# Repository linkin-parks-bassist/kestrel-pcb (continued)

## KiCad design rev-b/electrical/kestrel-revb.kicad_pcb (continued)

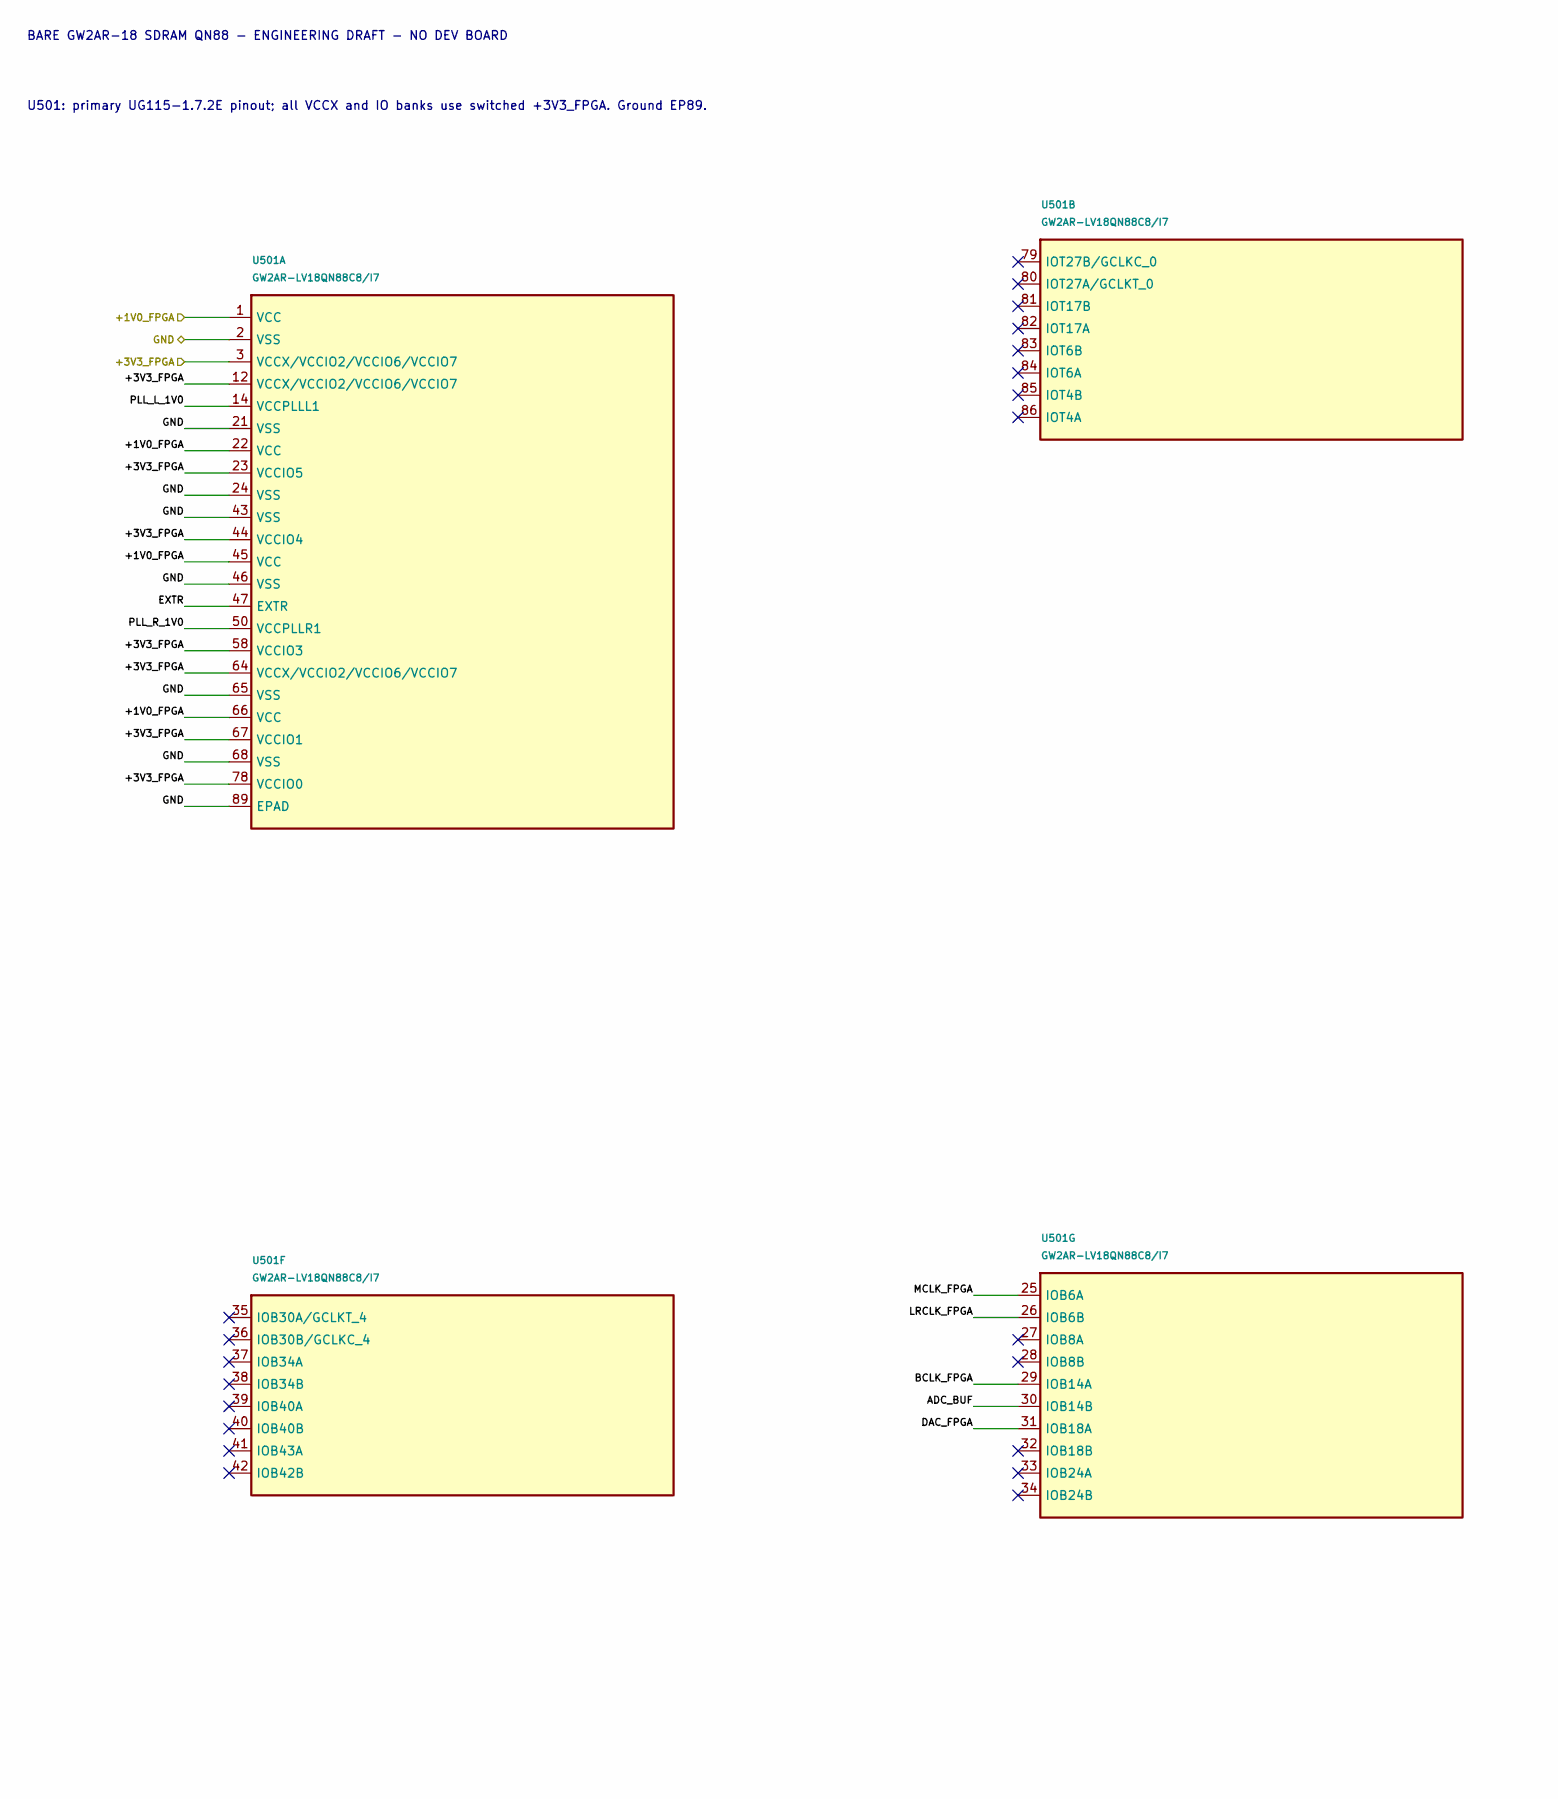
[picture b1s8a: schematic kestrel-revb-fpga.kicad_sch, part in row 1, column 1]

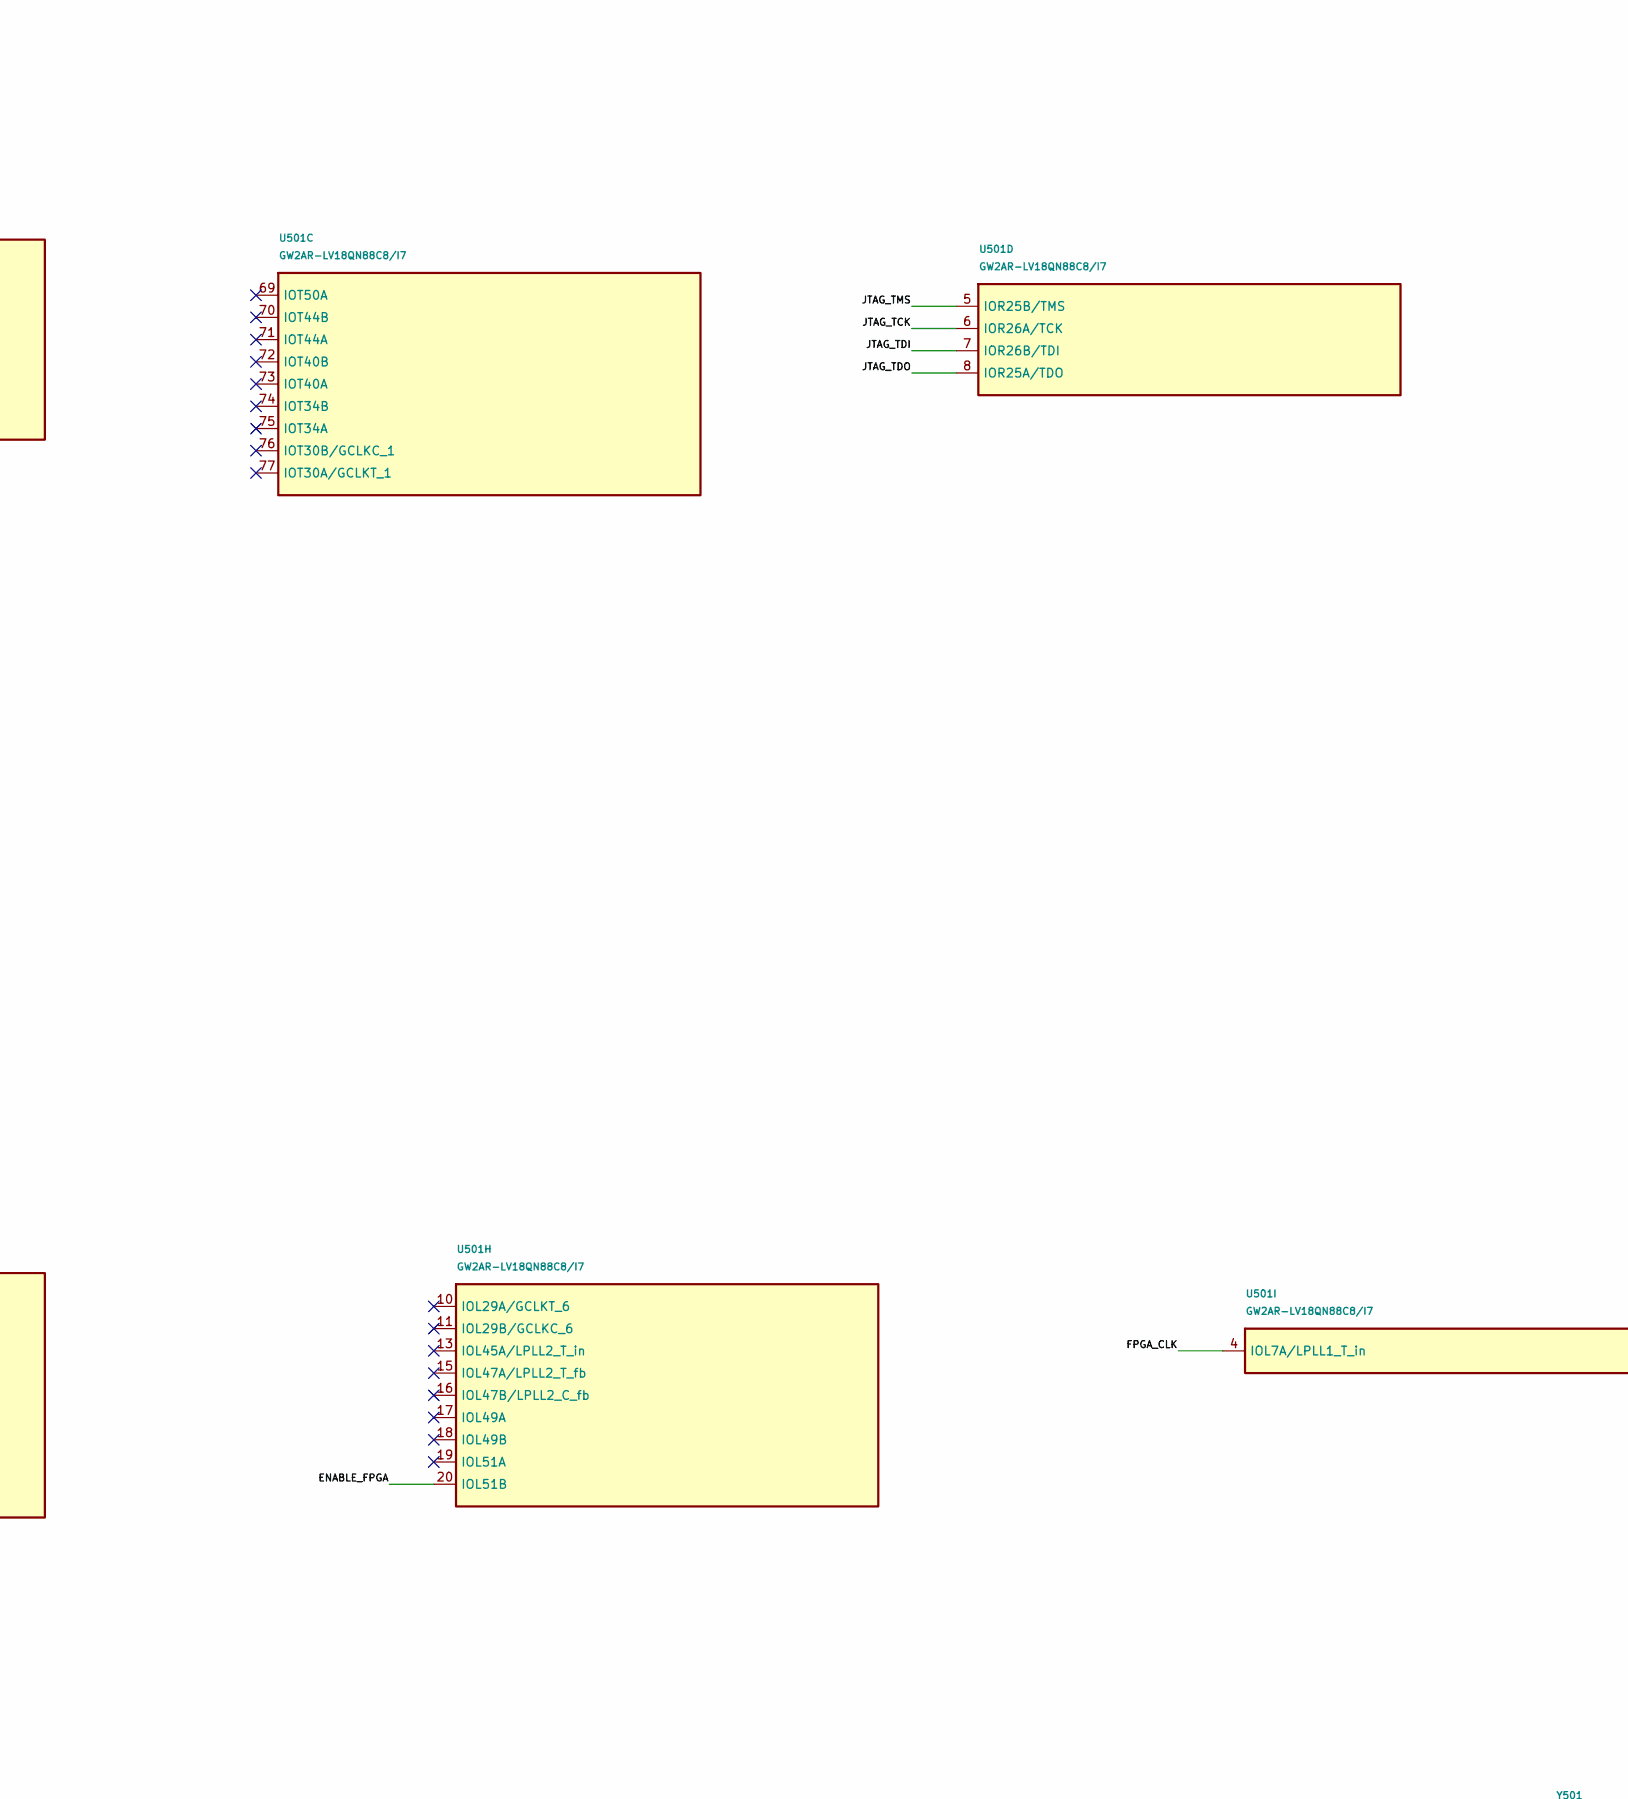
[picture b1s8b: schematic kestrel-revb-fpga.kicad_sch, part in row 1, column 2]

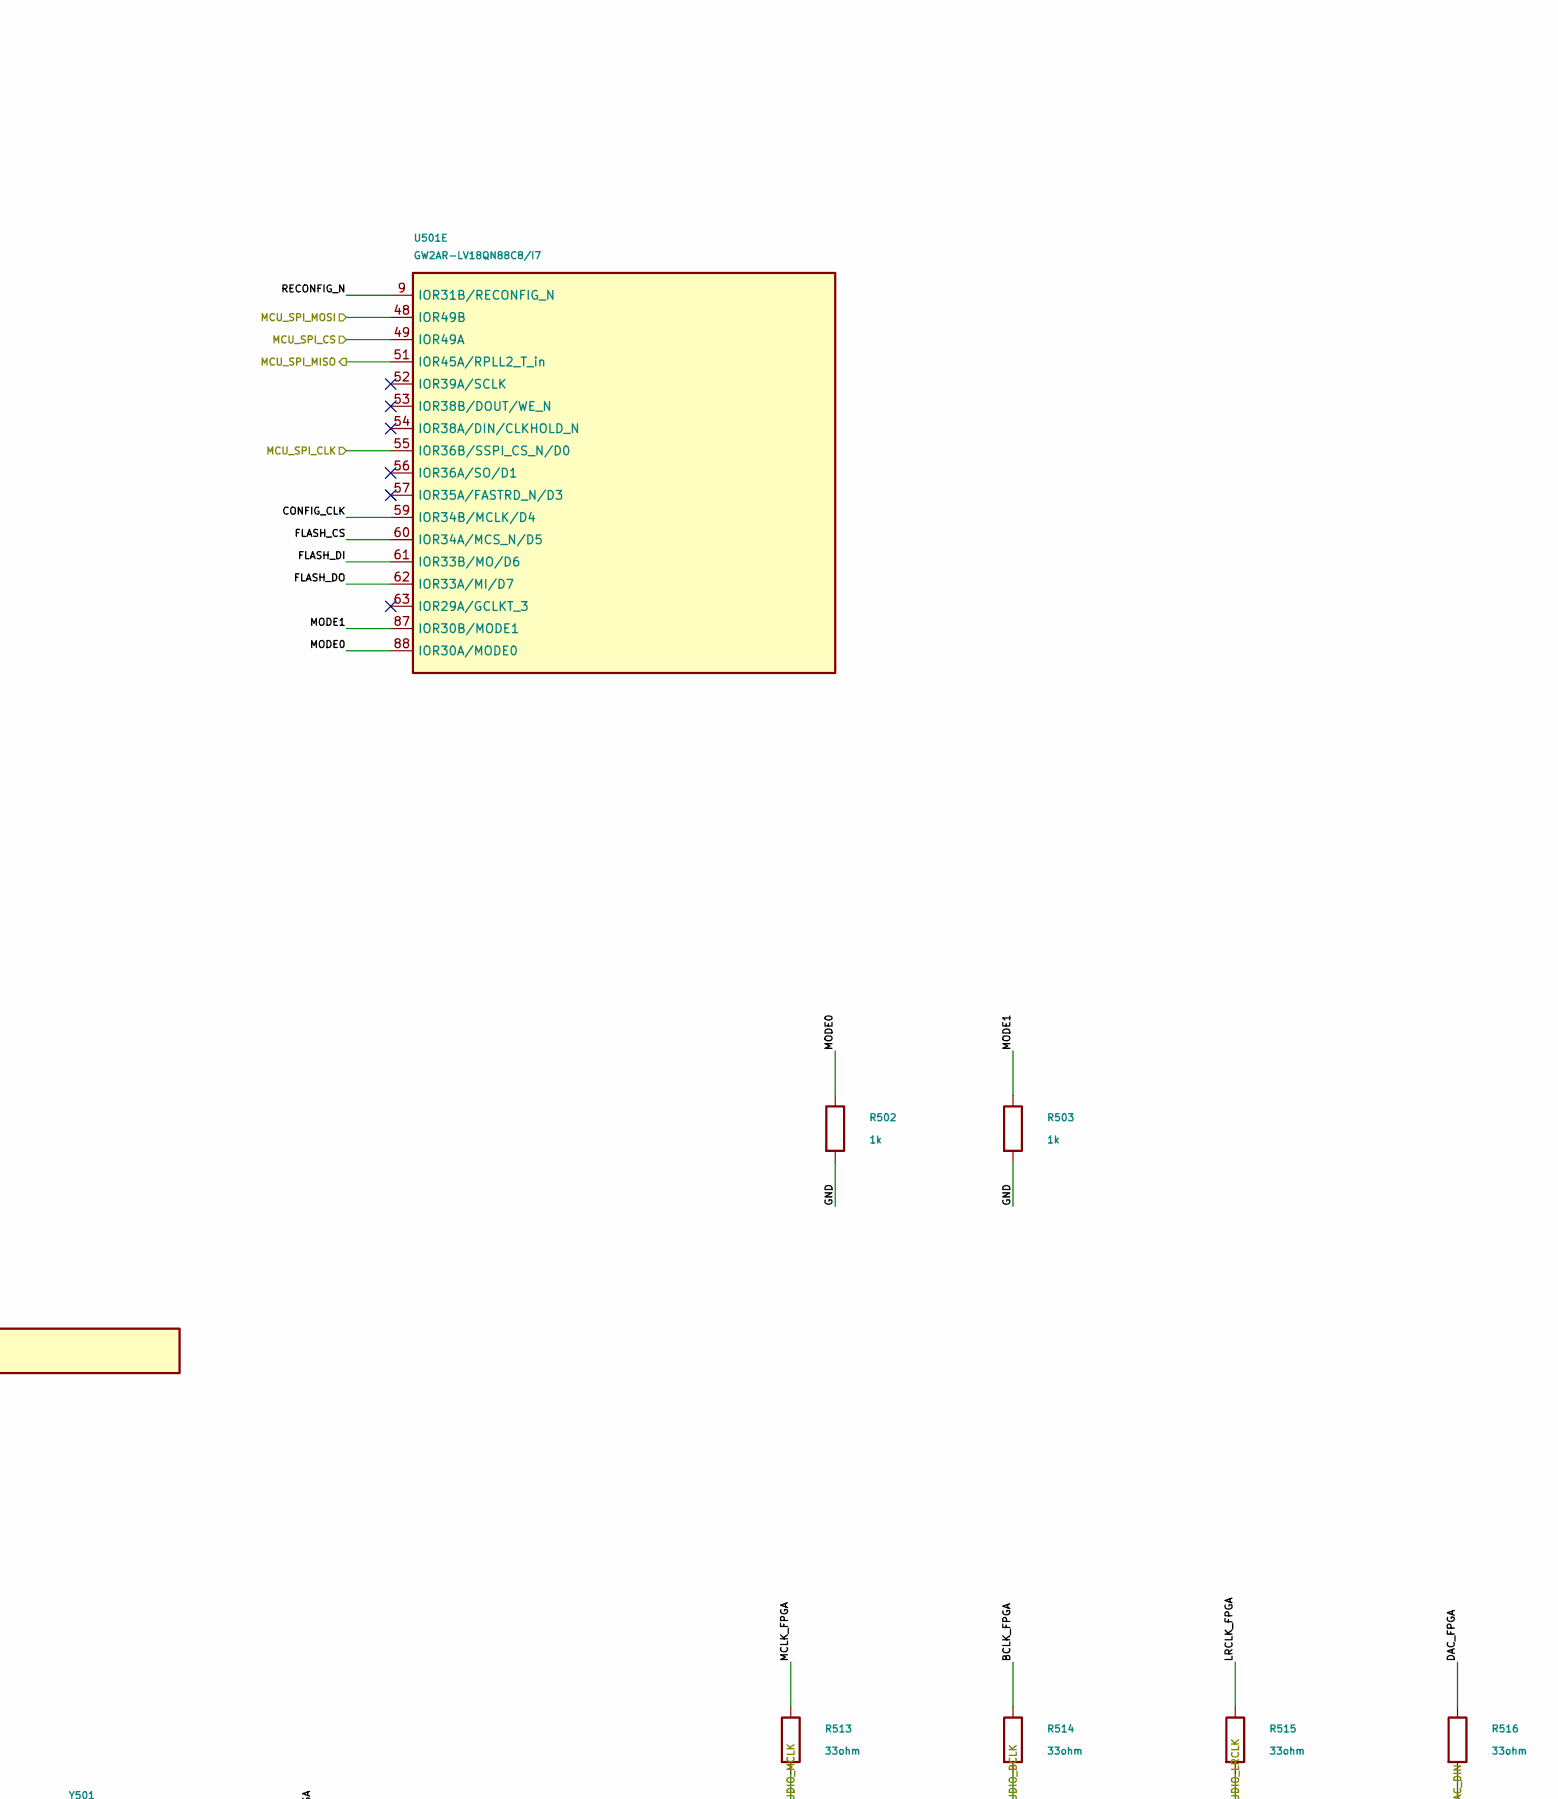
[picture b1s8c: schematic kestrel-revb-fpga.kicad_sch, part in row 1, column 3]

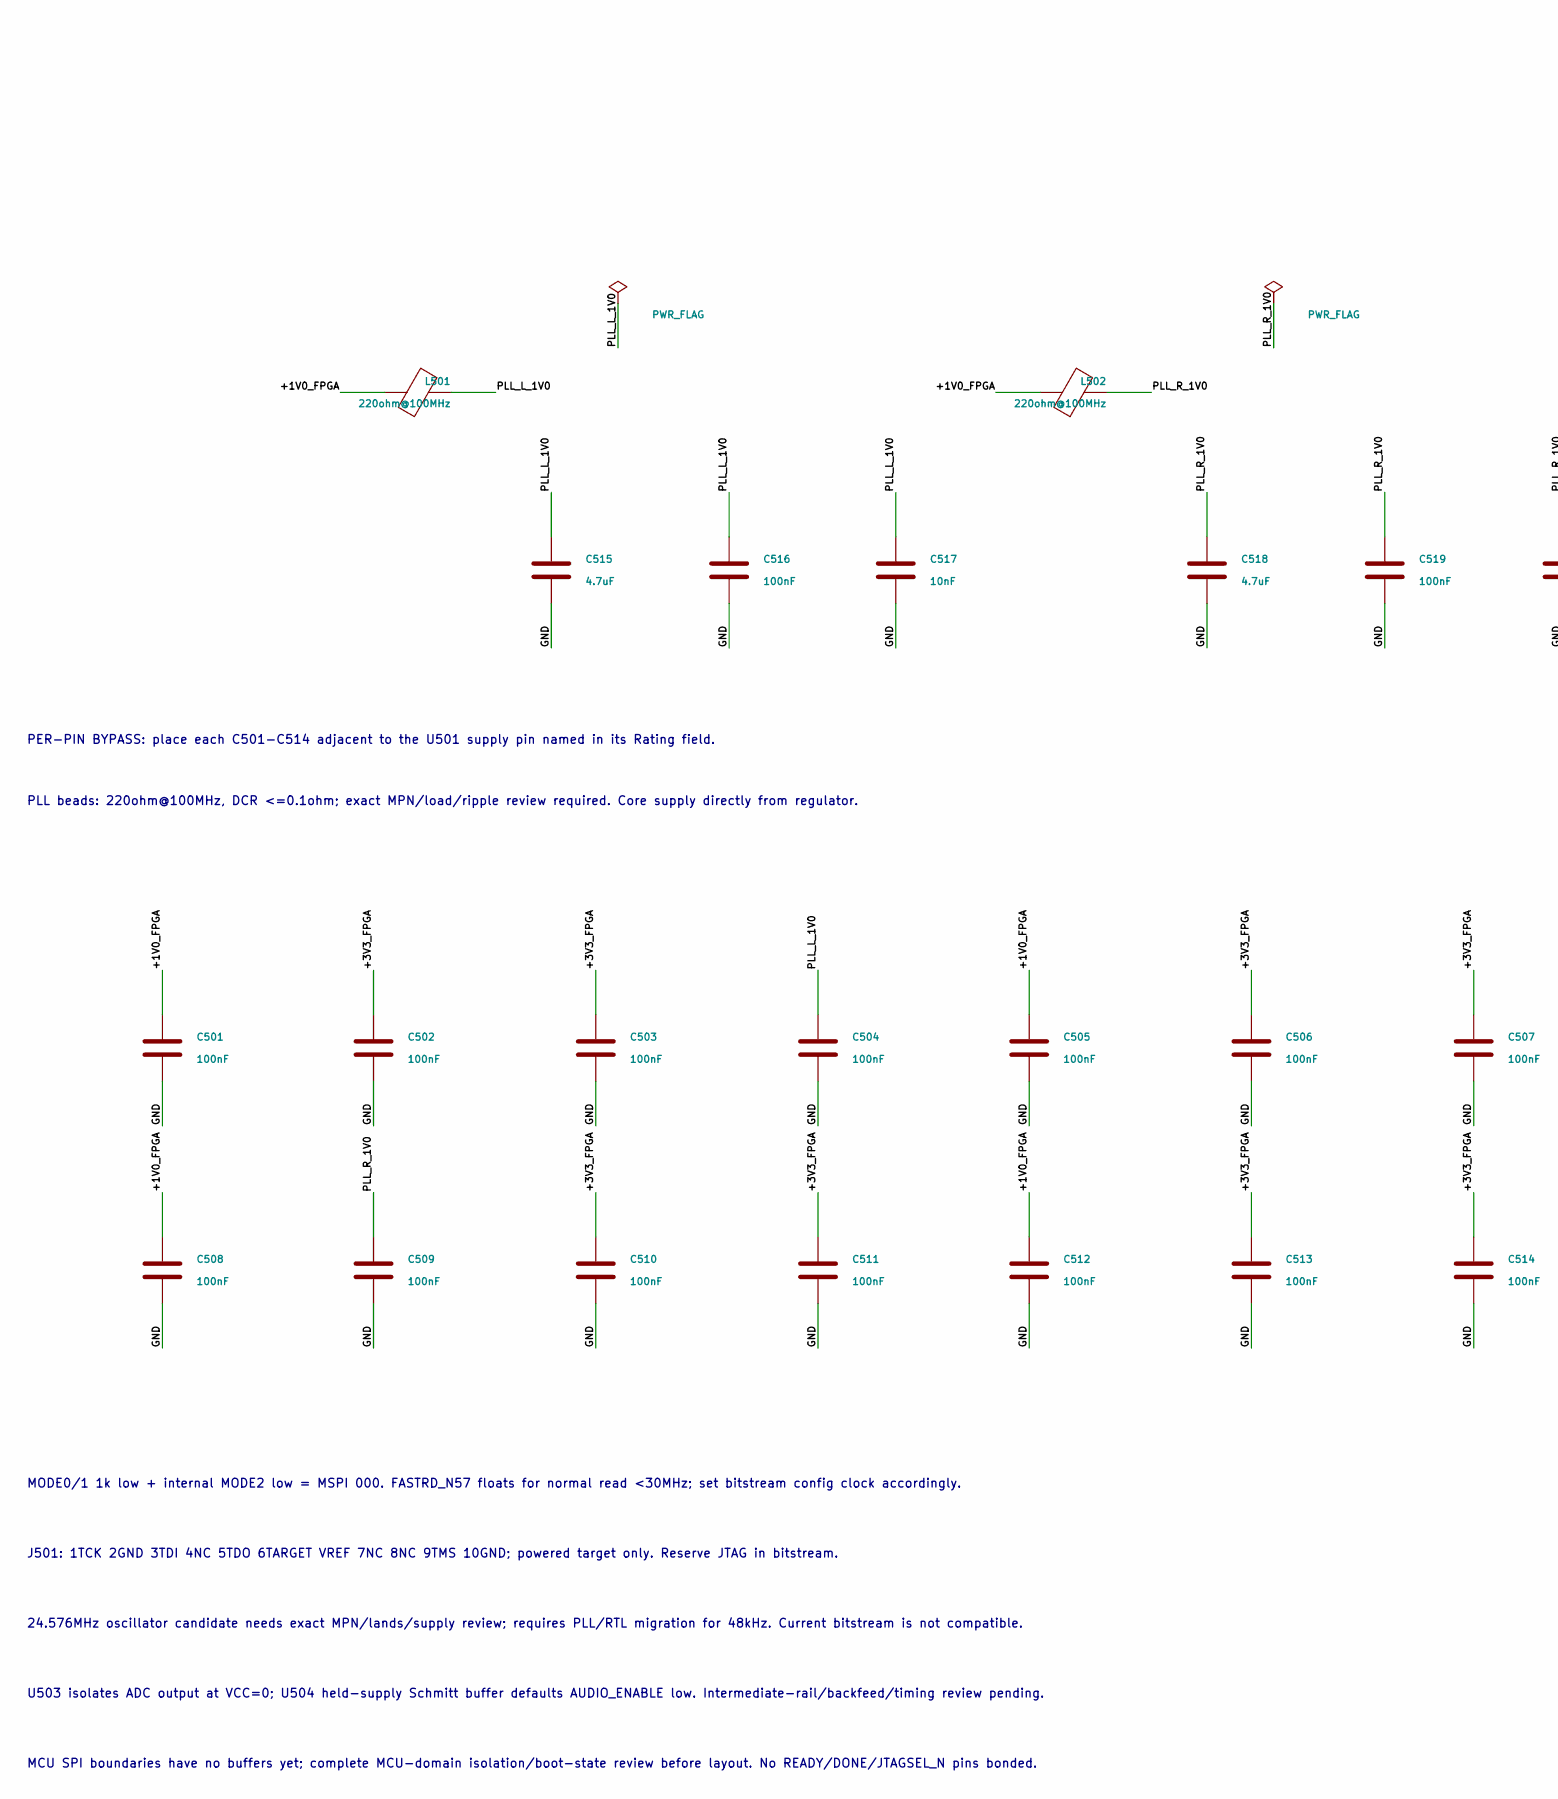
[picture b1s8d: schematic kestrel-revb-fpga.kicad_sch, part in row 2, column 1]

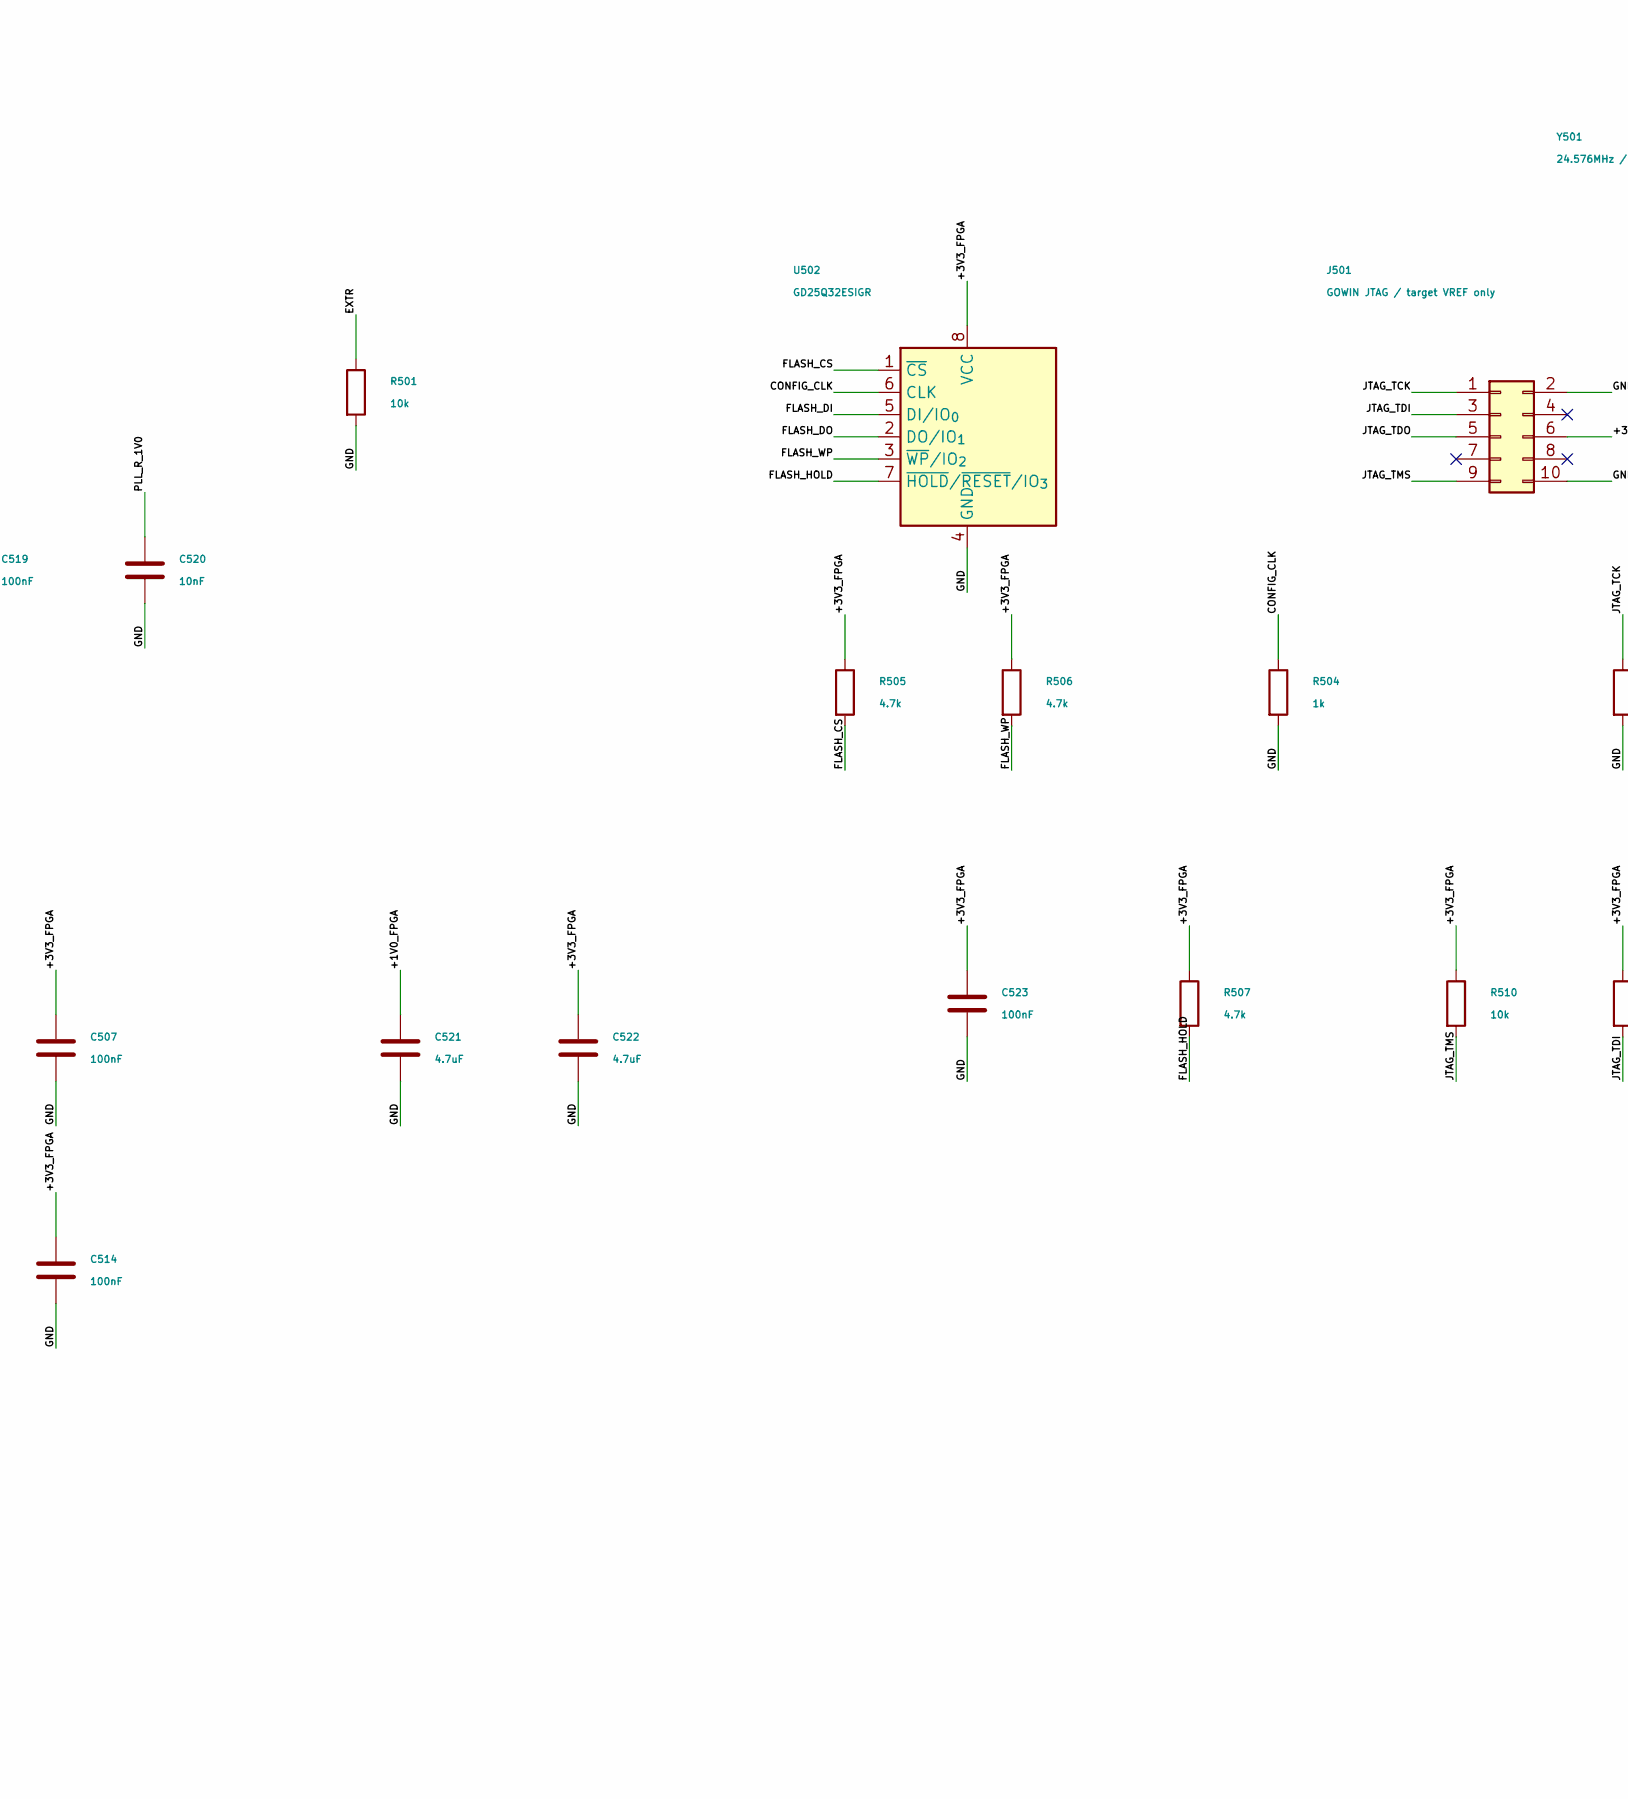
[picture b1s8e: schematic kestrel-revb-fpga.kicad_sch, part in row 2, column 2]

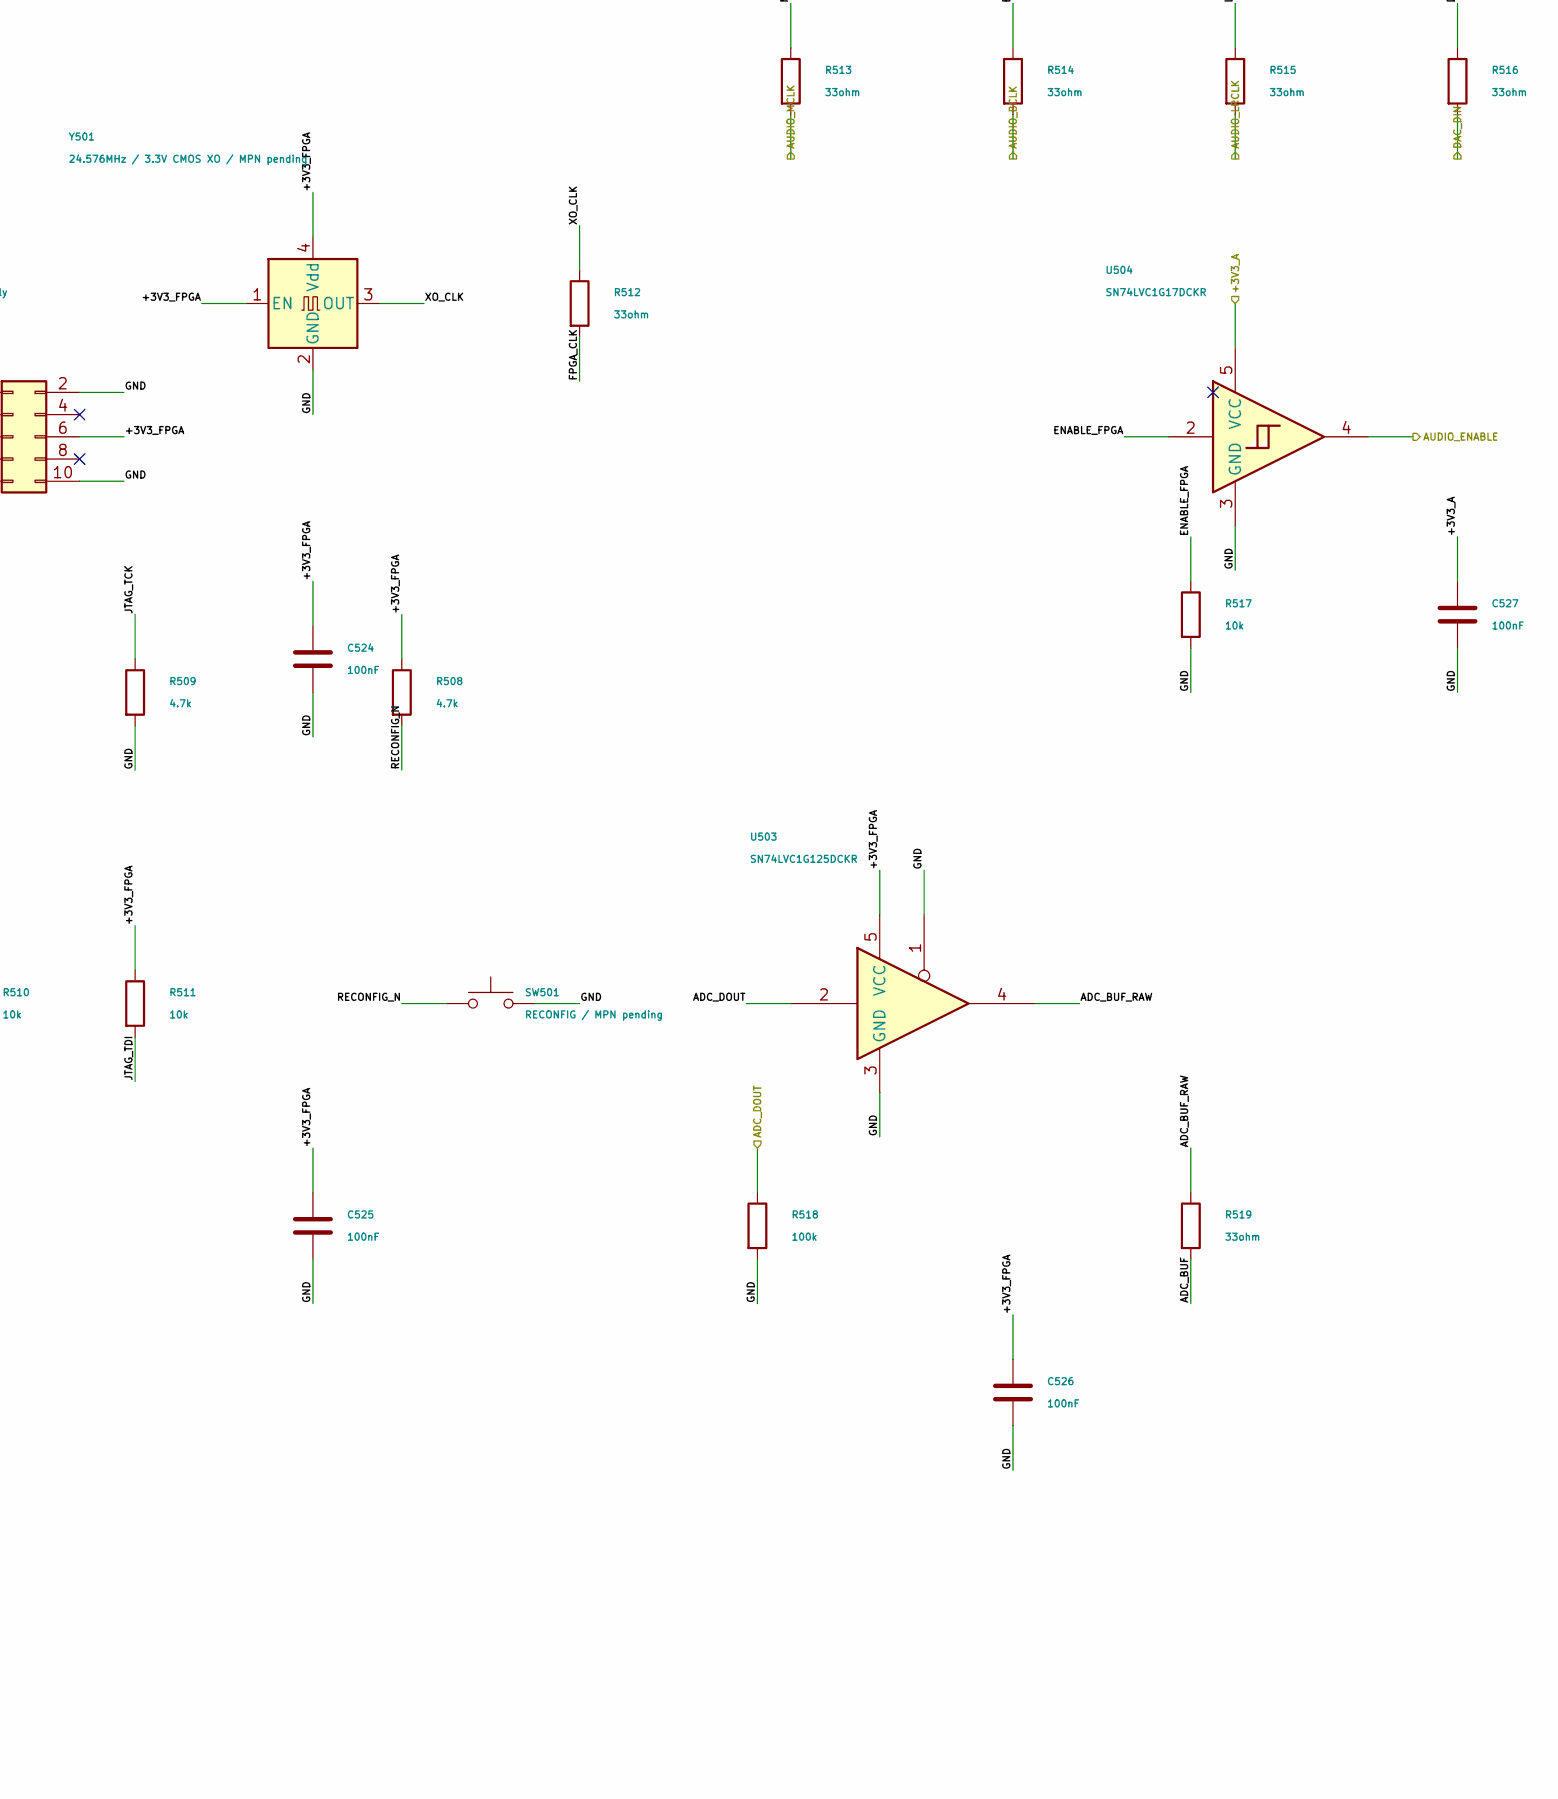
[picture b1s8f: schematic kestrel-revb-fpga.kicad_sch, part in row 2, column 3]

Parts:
C501: 100nF; C_0603_1608Metric; Rating 100nF / 16V X7R / at U501 pin 1
C502: 100nF; C_0603_1608Metric; Rating 100nF / 16V X7R / at U501 pin 3
C503: 100nF; C_0603_1608Metric; Rating 100nF / 16V X7R / at U501 pin 12
C504: 100nF; C_0603_1608Metric; Rating 100nF / 16V X7R / at U501 pin 14
C505: 100nF; C_0603_1608Metric; Rating 100nF / 16V X7R / at U501 pin 22
C506: 100nF; C_0603_1608Metric; Rating 100nF / 16V X7R / at U501 pin 23
C507: 100nF; C_0603_1608Metric; Rating 100nF / 16V X7R / at U501 pin 44
C508: 100nF; C_0603_1608Metric; Rating 100nF / 16V X7R / at U501 pin 45
C509: 100nF; C_0603_1608Metric; Rating 100nF / 16V X7R / at U501 pin 50
C510: 100nF; C_0603_1608Metric; Rating 100nF / 16V X7R / at U501 pin 58
C511: 100nF; C_0603_1608Metric; Rating 100nF / 16V X7R / at U501 pin 64
C512: 100nF; C_0603_1608Metric; Rating 100nF / 16V X7R / at U501 pin 66
C513: 100nF; C_0603_1608Metric; Rating 100nF / 16V X7R / at U501 pin 67
C514: 100nF; C_0603_1608Metric; Rating 100nF / 16V X7R / at U501 pin 78
C515, C518: 4.7uF; C_0603_1608Metric; Rating 4.7uF / 16V X7R
C516, C519, C523, C524, C526, C527: 100nF; C_0603_1608Metric; Rating 100nF / 16V X7R
C517, C520: 10nF; C_0603_1608Metric; Rating 10nF / 16V X7R
C521: 4.7uF; C_0603_1608Metric; Rating 4.7uF / 16V X7R / local core bulk
C522: 4.7uF; C_0603_1608Metric; Rating 4.7uF / 16V X7R / local IO bulk
C525: 100nF; C_0603_1608Metric; Rating 100nF / 16V X7R / JTAG VREF
J501: GOWIN JTAG / target VREF only; PinHeader_2x05_P2.54mm_Vertical
L501, L502: 220ohm@100MHz; L_0603_1608Metric; Rating 220ohm@100MHz / DCR <=0.1ohm / MPN pend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
R501, R510, R511, R517: 10k; R_0603_1608Metric; Rating 10k / 1%
R502, R503, R504: 1k; R_0603_1608Metric; Rating 1k / 1%
R505, R506, R507, R508, R509: 4.7k; R_0603_1608Metric; Rating 4.7k / 1%
R512, R513, R514, R515, R516, R519: 33ohm; R_0603_1608Metric; Rating 33ohm / 1%
R518: 100k; R_0603_1608Metric; Rating 100k / 1%
SW501: RECONFIG / MPN pending; SW_SPST_TL3342
U501: GW2AR-LV18QN88C8/I7; GW2AR_QN88_10x10_P0.4_EP6.8
U502: GD25Q32ESIGR; SOIC-8_5.3x5.3mm_P1.27mm
U503: SN74LVC1G125DCKR; SOT-353_SC-70-5
U504: SN74LVC1G17DCKR; SOT-353_SC-70-5
Y501: 24.576MHz / 3.3V CMOS XO / MPN pending; Oscillator_SMD_Abracon_ASE-4Pin_3.2x2.5mm

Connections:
/+1V0_FPGA: C501.1, C505.1, C508.1, C512.1, C521.1, L501.1, L502.1, U501.1 (VCC), U501.22 (VCC), U501.45 (VCC), U501.66 (VCC); also elsewhere on the board
/+3V3_A: C527.1, U504.5 (VCC); also elsewhere on the board
/+3V3_FPGA: C502.1, C503.1, C506.1, C507.1, C510.1, C511.1, C513.1, C514.1, C522.1, C523.1, C524.1, C525.1, C526.1, J501.6, R505.1, R506.1, R507.1, R508.1, R510.1, R511.1, U501.3 (VCCX/VCCIO2/VCCIO6/VCCIO7), U501.12 (VCCX/VCCIO2/VCCIO6/VCCIO7), U501.23 (VCCIO5), U501.44 (VCCIO4), U501.58 (VCCIO3), U501.64 (VCCX/VCCIO2/VCCIO6/VCCIO7), U501.67 (VCCIO1), U501.78 (VCCIO0), U502.8 (VCC), U503.5 (VCC), Y501.1 (EN), Y501.4 (Vdd); also elsewhere on the board
/ADC_DOUT: R518.1, U503.2; also elsewhere on the board
/AUDIO_BCLK: R514.2; also elsewhere on the board
/AUDIO_ENABLE: U504.4; also elsewhere on the board
/AUDIO_LRCLK: R515.2; also elsewhere on the board
/AUDIO_MCLK: R513.2; also elsewhere on the board
/Bare GW2AR-18 support/ADC_BUF: R519.2, U501.30 (IOB14B)
/Bare GW2AR-18 support/ADC_BUF_RAW: R519.1, U503.4
/Bare GW2AR-18 support/BCLK_FPGA: R514.1, U501.29 (IOB14A)
/Bare GW2AR-18 support/CONFIG_CLK: R504.1, U501.59 (IOR34B/MCLK/D4), U502.6 (CLK)
/Bare GW2AR-18 support/DAC_FPGA: R516.1, U501.31 (IOB18A)
/Bare GW2AR-18 support/ENABLE_FPGA: R517.1, U501.20 (IOL51B), U504.2
/Bare GW2AR-18 support/EXTR: R501.1, U501.47 (EXTR)
/Bare GW2AR-18 support/FLASH_CS: R505.2, U501.60 (IOR34A/MCS_N/D5), U502.1 (~CS)
/Bare GW2AR-18 support/FLASH_DI: U501.61 (IOR33B/MO/D6), U502.5 (DI/IO_{0})
/Bare GW2AR-18 support/FLASH_DO: U501.62 (IOR33A/MI/D7), U502.2 (DO/IO_{1})
/Bare GW2AR-18 support/FLASH_HOLD: R507.2, U502.7 (~HOLD/~RESET/IO_{3})
/Bare GW2AR-18 support/FLASH_WP: R506.2, U502.3 (~WP/IO_{2})
/Bare GW2AR-18 support/FPGA_CLK: R512.2, U501.4 (IOL7A/LPLL1_T_in)
/Bare GW2AR-18 support/JTAG_TCK: J501.1, R509.1, U501.6 (IOR26A/TCK)
/Bare GW2AR-18 support/JTAG_TDI: J501.3, R511.2, U501.7 (IOR26B/TDI)
/Bare GW2AR-18 support/JTAG_TDO: J501.5, U501.8 (IOR25A/TDO)
/Bare GW2AR-18 support/JTAG_TMS: J501.9, R510.2, U501.5 (IOR25B/TMS)
/Bare GW2AR-18 support/LRCLK_FPGA: R515.1, U501.26 (IOB6B)
/Bare GW2AR-18 support/MCLK_FPGA: R513.1, U501.25 (IOB6A)
/Bare GW2AR-18 support/MODE0: R502.1, U501.88 (IOR30A/MODE0)
/Bare GW2AR-18 support/MODE1: R503.1, U501.87 (IOR30B/MODE1)
/Bare GW2AR-18 support/PLL_L_1V0: C504.1, C515.1, C516.1, C517.1, L501.2, U501.14 (VCCPLLL1)
/Bare GW2AR-18 support/PLL_R_1V0: C509.1, C518.1, C519.1, C520.1, L502.2, U501.50 (VCCPLLR1)
/Bare GW2AR-18 support/RECONFIG_N: R508.2, SW501.1, U501.9 (IOR31B/RECONFIG_N)
/Bare GW2AR-18 support/XO_CLK: R512.1, Y501.3 (OUT)
/DAC_DIN: R516.2; also elsewhere on the board
/GND: C501.2, C502.2, C503.2, C504.2, C505.2, C506.2, C507.2, C508.2, C509.2, C510.2, C511.2, C512.2, C513.2, C514.2, C515.2, C516.2, C517.2, C518.2, C519.2, C520.2, C521.2, C522.2, C523.2, C524.2, C525.2, C526.2, C527.2, J501.2, J501.10, R501.2, R502.2, R503.2, R504.2, R509.2, R517.2, R518.2, SW501.2, U501.2 (VSS), U501.21 (VSS), U501.24 (VSS), U501.43 (VSS), U501.46 (VSS), U501.65 (VSS), U501.68 (VSS), U501.89 (EPAD), U502.4 (GND), U503.1, U503.3 (GND), U504.3 (GND), Y501.2 (GND); also elsewhere on the board
/MCU_SPI_CLK: U501.55 (IOR36B/SSPI_CS_N/D0); also elsewhere on the board
/MCU_SPI_CS: U501.49 (IOR49A); also elsewhere on the board
/MCU_SPI_MISO: U501.51 (IOR45A/RPLL2_T_in); also elsewhere on the board
/MCU_SPI_MOSI: U501.48 (IOR49B); also elsewhere on the board

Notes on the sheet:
BARE GW2AR-18 SDRAM QN88 - ENGINEERING DRAFT - NO DEV BOARD
U501: primary UG115-1.7.2E pinout; all VCCX and IO banks use switched +3V3_FPGA. Ground EP89.
PER-PIN BYPASS: place each C501-C514 adjacent to the U501 supply pin named in its Rating field.
PLL beads: 220ohm@100MHz, DCR <=0.1ohm; exact MPN/load/ripple review required. Core supply directly from regulator.
MODE0/1 1k low + internal MODE2 low = MSPI 000. FASTRD_N57 floats for normal read <30MHz; set bitstream config clock accordingly.
J501: 1TCK 2GND 3TDI 4NC 5TDO 6TARGET VREF 7NC 8NC 9TMS 10GND; powered target only. Reserve JTAG in bitstream.
24.576MHz oscillator candidate needs exact MPN/lands/supply review; requires PLL/RTL migration for 48kHz. Current bitstream is not compatible.
U503 isolates ADC output at VCC=0; U504 held-supply Schmitt buffer defaults AUDIO_ENABLE low. Intermediate-rail/backfeed/timing review pending.
MCU SPI boundaries have no buffers yet; complete MCU-domain isolation/boot-state review before layout. No READY/DONE/JTAGSEL_N pins bonded.

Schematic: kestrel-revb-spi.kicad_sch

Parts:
C801, C802: 100nF; C_0402_1005Metric; Rating 100nF / 16V X7R / local bypass; MPN CL05B104KO5NNNC; LCSC C1525
C803, C804: 100nF; C_0603_1608Metric; Rating 100nF / 16V X7R / local bypass
C805: 1nF; C_0603_1608Metric; Rating 1nF / 25V C0G / SENSE filter
R801, R802, R803, R804: 33ohm; R_0603_1608Metric; Rating 33ohm / output damping / tune on PCB
R805: 4.7k; R_0603_1608Metric; Rating 4.7k / 1% / FPGA CS idle
R806: 4.7k; R_0603_1608Metric; Rating 4.7k / 1% / MCU CS idle
R807: 10k; R_0603_1608Metric; Rating 10k / 1% / OE default disabled
R808: 10k; R_0603_1608Metric; Rating 10k / 1% / firmware enable default off
R809: 10k; R_0603_1608Metric; Rating 10k / 1% / open drain release pullup
R810: 63.4k; R_0603_1608Metric; Rating 63.4k / 0.1% / IO monitor high
R811: 10k; R_0603_1608Metric; Rating 10k / 0.1% / IO monitor low
U801: SN74AXC4T774PWR; TSSOP-16_4.4x5mm_P0.65mm
U802: TPS3808G01DBVR; SOT-23-6
U803: SN74LVC1G00DCKR; Texas_R-PDSO-G5_DCK-5

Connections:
/+3V3_D: C801.1, C803.1, C804.1, R806.1, R807.1, R809.1, U801.1 (DIR1), U801.2 (DIR2), U801.7 (DIR3), U801.16 (VCCA), U802.6 (VDD), U803.5 (VCC); also elsewhere on the board
/+3V3_FPGA: C802.1, R805.1, R810.1, U801.15 (VCCB); also elsewhere on the board
/GND: C801.2, C802.2, C803.2, C804.2, C805.2, R808.2, R811.2, U801.8 (DIR4), U801.10 (GND), U802.2 (GND), U803.3 (GND); also elsewhere on the board
/MCU_RAW_CLK: U801.4 (A2_CLK); also elsewhere on the board
/MCU_RAW_CS: R806.2, U801.3 (A1_CS); also elsewhere on the board
/MCU_RAW_MISO: R804.2; also elsewhere on the board
/MCU_RAW_MOSI: U801.5 (A3_MOSI); also elsewhere on the board
/MCU_RESET_N: U802.3 (~MR); also elsewhere on the board
/MCU_SPI_CLK: R802.2; also elsewhere on the board
/MCU_SPI_CS: R801.2, R805.2; also elsewhere on the board
/MCU_SPI_ENABLE: R808.1, U803.1; also elsewhere on the board
/MCU_SPI_MISO: U801.11 (B4_MISO); also elsewhere on the board
/MCU_SPI_MOSI: R803.2; also elsewhere on the board
/Power-domain SPI isolation/SPI_CLK_B: R802.1, U801.13 (B2_CLK)
/Power-domain SPI isolation/SPI_CS_B: R801.1, U801.14 (B1_CS)
/Power-domain SPI isolation/SPI_MISO_A: R804.1, U801.6 (A4_MISO)
/Power-domain SPI isolation/SPI_MOSI_B: R803.1, U801.12 (B3_MOSI)
/Power-domain SPI isolation/SPI_OE_N: R807.2, U801.9 (OE_N), U803.4
/Power-domain SPI isolation/SPI_RAIL_RELEASE: R809.2, U802.1 (~RESET), U803.2
/Power-domain SPI isolation/SPI_SENSE: C805.1, R810.2, R811.1, U802.5 (SENSE)

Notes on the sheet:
SPI POWER-DOMAIN BRIDGE - ENGINEERING DRAFT
GPIO7 enable defaults low. OE = NOT(enable AND rail release). MCU reset restarts supervisor delay.
63.4k/10k divider: nominal falling trip 2.9727V; CT open 12-28ms release. This is an isolation guard, not FPGA-valid proof.
Firmware must set CS high / CLK low before enabling, await FPGA configuration, and disable before controlled shutdown.
Ioff / VCC<100mV isolation; arbitrary ramps, 10MHz timing, pullup margins and Sydney sourcing remain to qualify.
